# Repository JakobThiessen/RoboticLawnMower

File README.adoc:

= RoboticLawnMower
:TOC:

== Projektbeschreibung
Rasenmähroboter in Eigenbau

== Konzept

image::docs/Konzept_1.drawio.svg[static, 600]

== Projektübersicht

== Hardware
image::Hardware/KiCad/RoboticLawnMower/3D_TOP.png[static, 600]

image::Hardware/KiCad/RoboticLawnMower/3D_BOT.png[static, 600]

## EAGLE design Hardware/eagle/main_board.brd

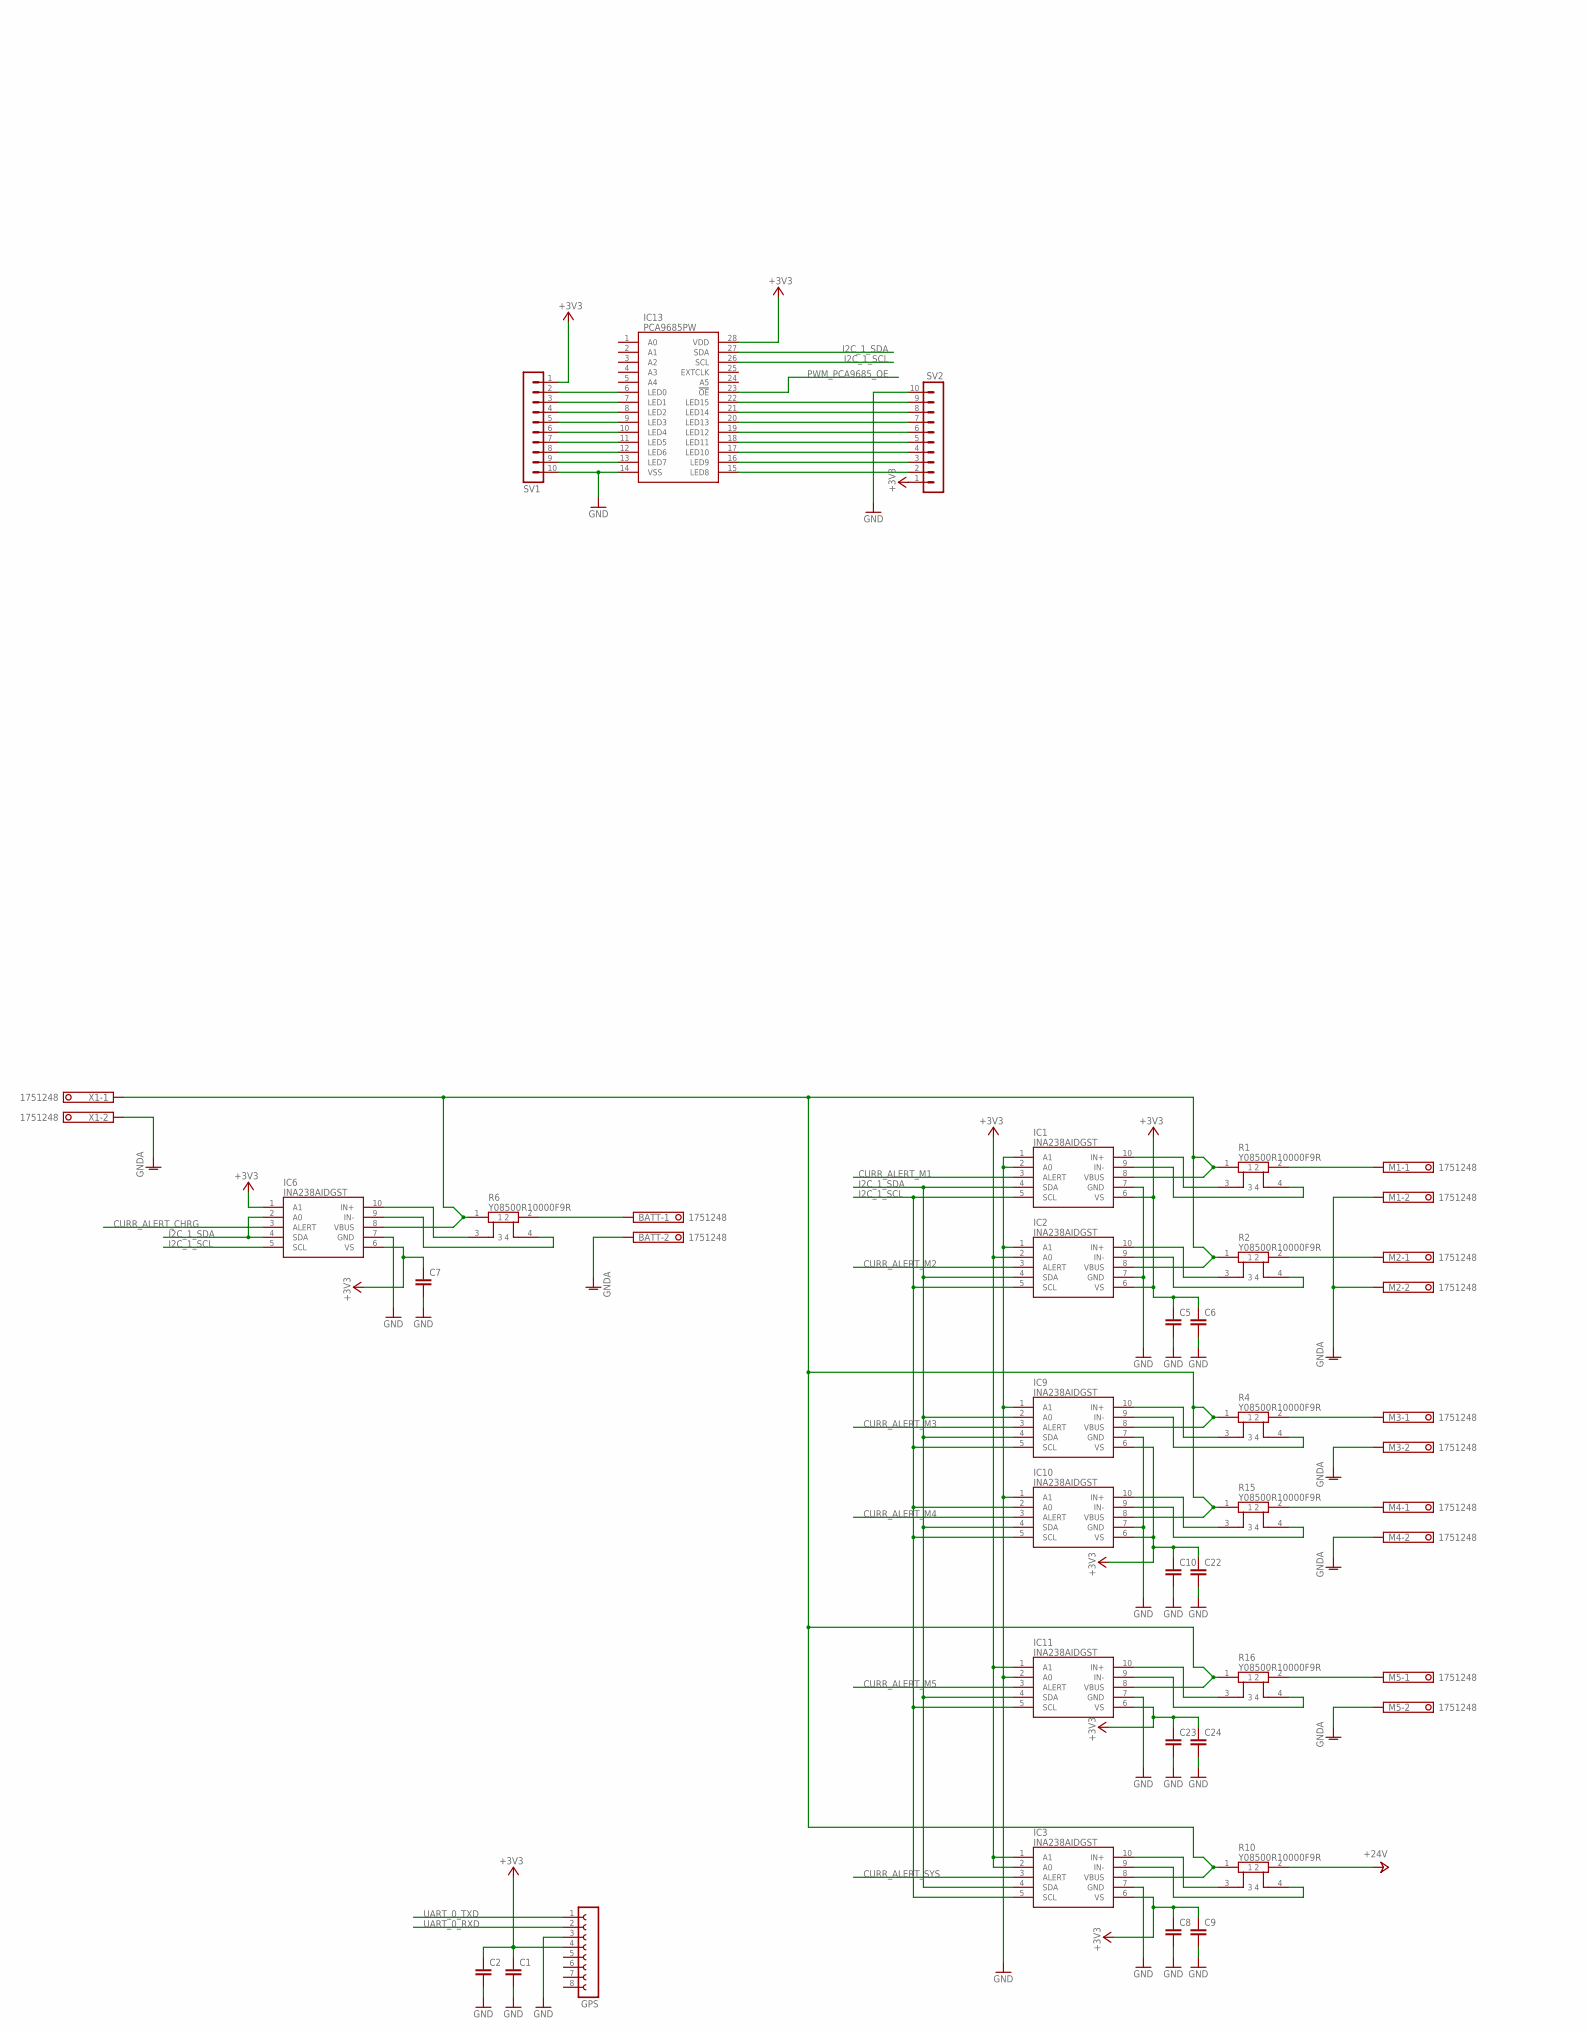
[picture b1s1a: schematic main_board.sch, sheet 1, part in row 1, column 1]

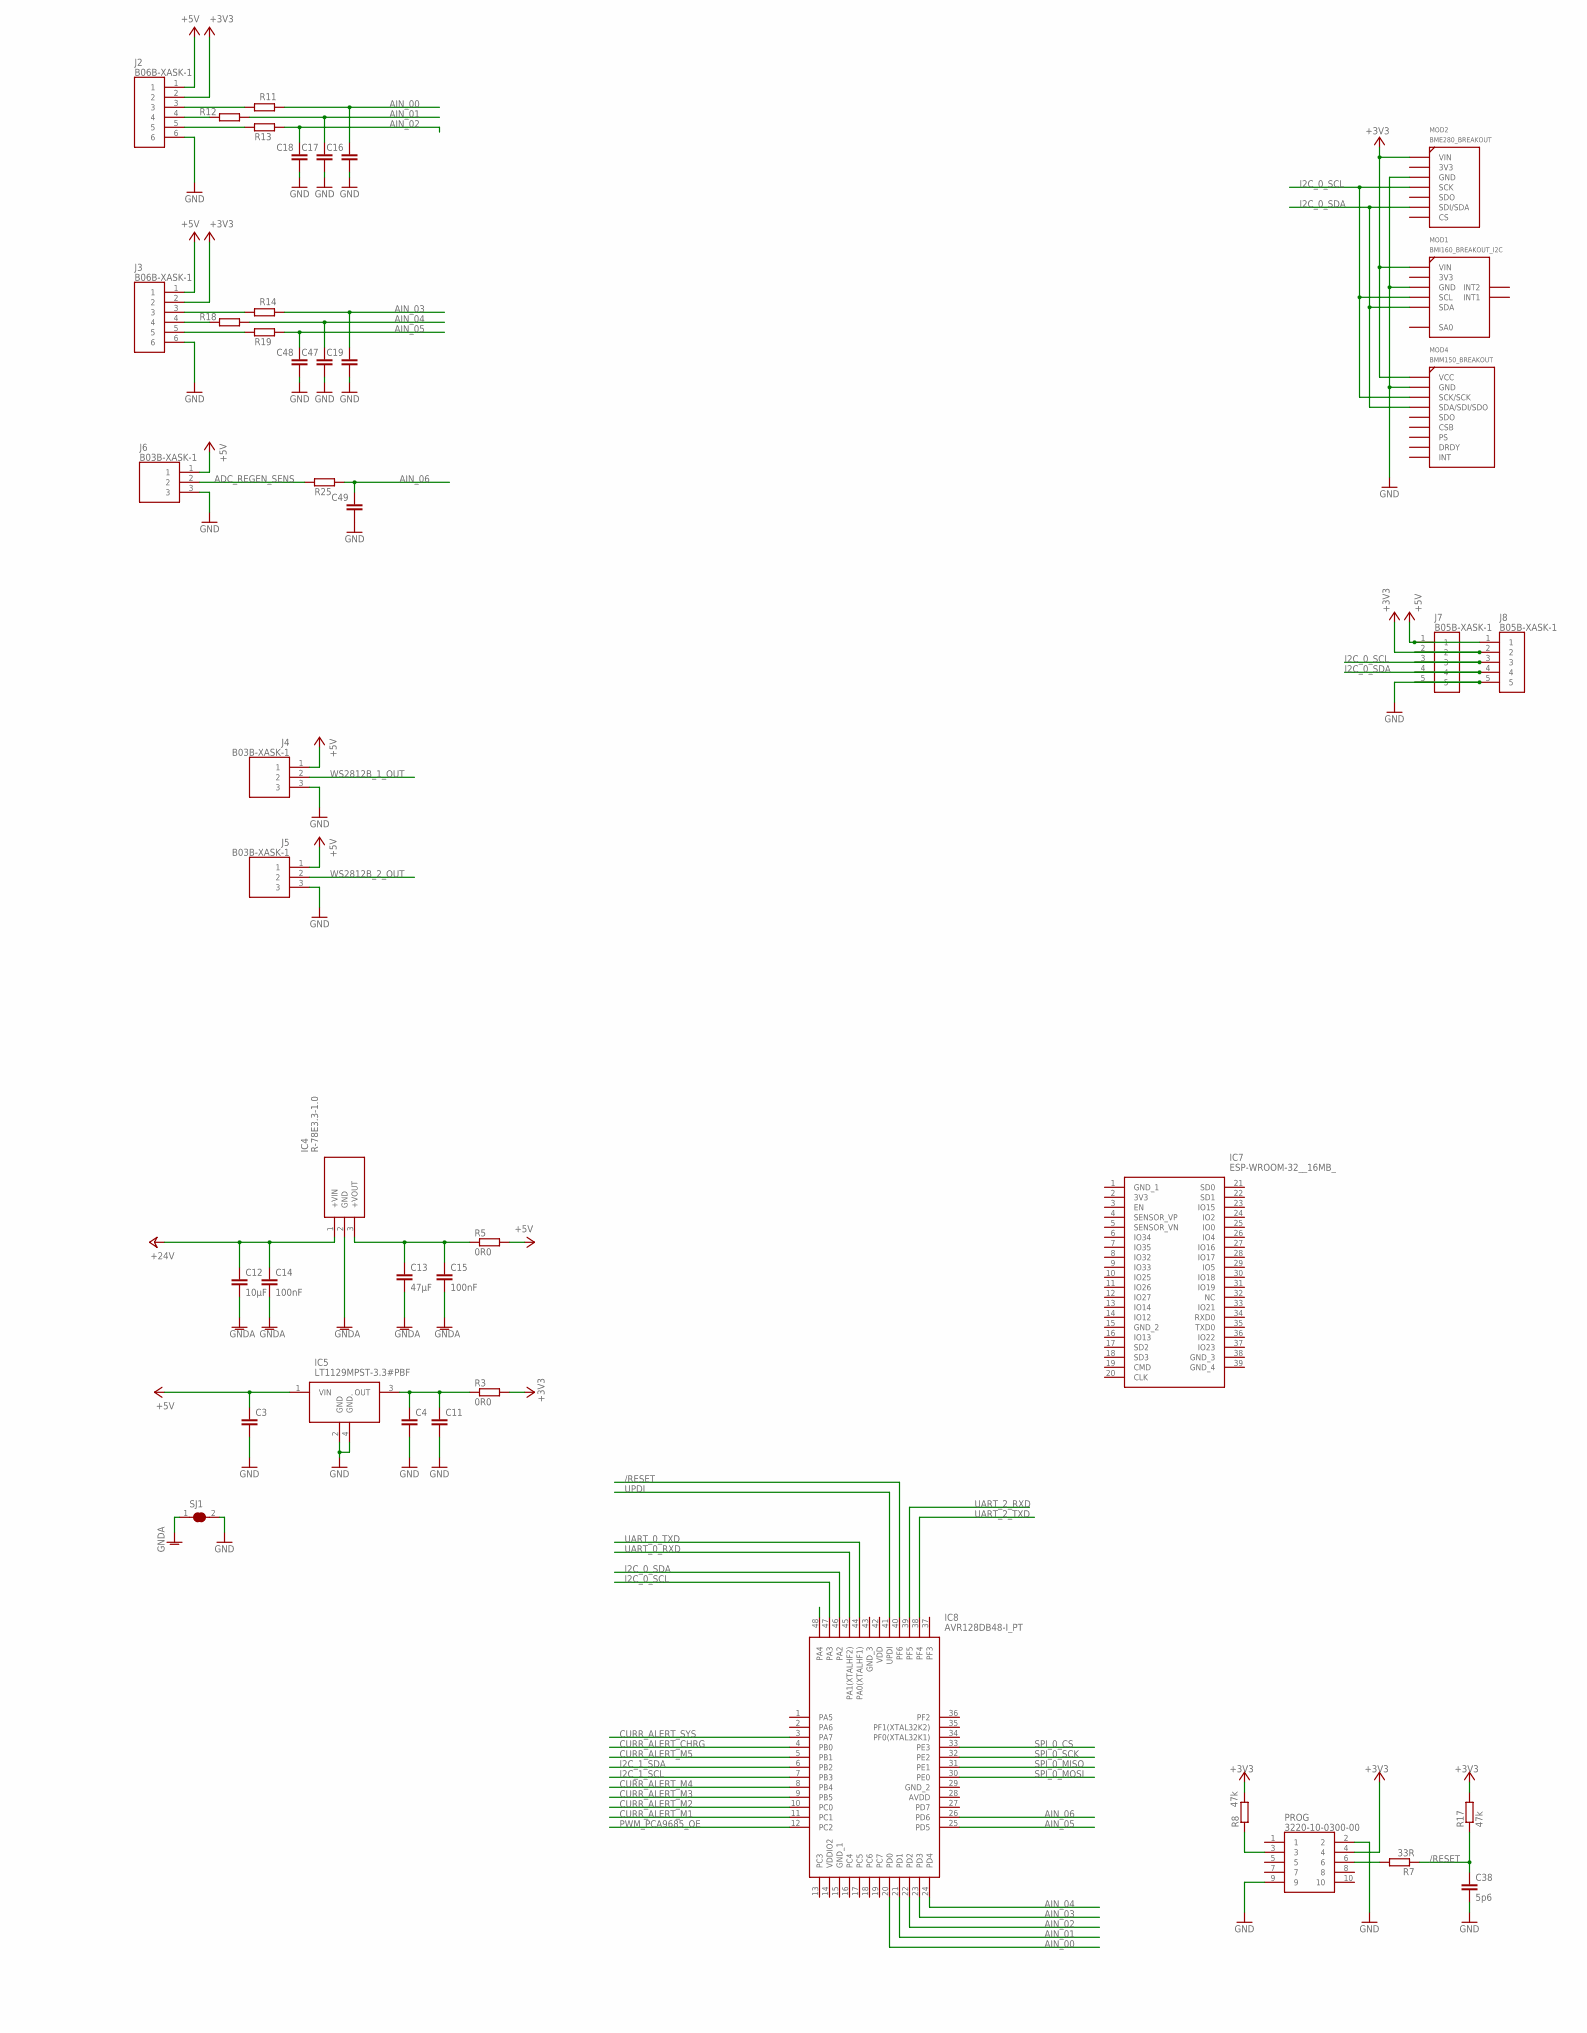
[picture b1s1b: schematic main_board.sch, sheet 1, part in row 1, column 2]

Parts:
BATT: 1751248
C1, C2, C3, C4, C5, C6, C7, C8, C9, C10, C11, C16, C17, C18, C19, C22, C23, C24, C47, C48, C49: C-EUC0603; C0603
C12: 10µF; C1210
C13: 47µF; C1210
C14, C15: 100nF; C0603
C38: 5p6; C0603
GPS: FE08-1; FE08
IC1, IC2, IC3, IC6, IC9, IC10, IC11: INA238AIDGST; SOP50P490X110-10N
IC4: R-78E3.3-1.0; R78E3310
IC5: LT1129MPST-3.3#PBF; SOT230P700X180-4N
IC7: ESP-WROOM-32__16MB_; ESP32WROOM32D
IC8: AVR128DB48-I_PT; QFP50P900X900X120-48N
IC13: PCA9685PW; SOP65P640X110-28N
J2, J3: B06B-XASK-1; SHDR6W60P0X250_1X6_1750X640X88
J4, J5, J6: B03B-XASK-1; SHDR3W60P0X250_1X3_1000X640X88
J7, J8: B05B-XASK-1; SHDR5W60P0X250_1X5_1500X640X88
M1, M2, M3, M4, M5: 1751248
MOD1: BMI160_BREAKOUT_I2C
MOD2: BME280_BREAKOUT
MOD4: BMM150_BREAKOUT
PROG: 3220-10-0300-00
R1, R2, R4, R6, R10, R15, R16: Y08500R10000F9R
R3, R5: 0R0; R0603
R7: 33R; R0603
R8, R17: 47k; R0603
R11, R12, R13, R14, R18, R19, R25: R-EU_R0603; R0603
SJ1: SOLDERJUMPER_CLOSEDPERM
SV1, SV2: MA10-1
X1: 1751248

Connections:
+3V3: C1.1, C2.1, C5.1, C6.1, C7.1, C8.1, C9.1, C10.1, C22.1, C23.1, C24.1, GPS.4, IC1.6 (VS), IC2.2 (A0), IC2.6 (VS), IC3.1 (A1), IC3.2 (A0), IC3.6 (VS), IC6.1 (A1), IC6.6 (VS), IC9.6 (VS), IC10.6 (VS), IC11.1 (A1), IC11.6 (VS), IC13.28 (VDD), J2.2, J3.2, J7.2, J8.2, MOD1.P$1 (VIN), MOD2.P$1 (VIN), MOD4.P$1 (VCC), PROG.4, R3.2, R8.2, R17.2, SV1.1, SV2.1
+5V: C3.1, IC5.1 (VIN), J2.1, J3.1, J4.1, J5.1, J6.1, J7.1, J8.1, R5.2
+24V: C12.1, C14.1, IC4.1 (+VIN), R10.2
+24V2: IC1.8 (VBUS), IC2.8 (VBUS), IC3.8 (VBUS), IC6.8 (VBUS), IC9.8 (VBUS), IC10.8 (VBUS), IC11.8 (VBUS), R1.1, R2.1, R4.1, R6.1, R10.1, R15.1, R16.1, X1.1
/RESET: C38.1, IC8.40 (PF6), R7.1, R17.1
ADC_REGEN_SENS: J6.2, R25.1
AIN_00: C16.1, IC8.20 (PD0), R11.2
AIN_01: C17.1, IC8.21 (PD1), R12.2
AIN_02: C18.1, IC8.22 (PD2), R13.2
AIN_03: C19.1, IC8.23 (PD3), R14.2
AIN_04: C47.1, IC8.24 (PD4), R18.2
AIN_05: C48.1, IC8.25 (PD5), R19.2
AIN_06: C49.1, IC8.26 (PD6), R25.2
CURR_ALERT_CHRG: IC6.3 (ALERT), IC8.4 (PB0)
CURR_ALERT_M1: IC1.3 (ALERT), IC8.11 (PC1)
CURR_ALERT_M2: IC2.3 (ALERT), IC8.10 (PC0)
CURR_ALERT_M3: IC8.9 (PB5), IC9.3 (ALERT)
CURR_ALERT_M4: IC8.8 (PB4), IC10.3 (ALERT)
CURR_ALERT_M5: IC8.5 (PB1), IC11.3 (ALERT)
CURR_ALERT_SYS: IC3.3 (ALERT), IC8.3 (PA7)
GND: C1.2, C2.2, C3.2, C4.2, C5.2, C6.2, C7.2, C8.2, C9.2, C10.2, C11.2, C16.2, C17.2, C18.2, C19.2, C22.2, C23.2, C24.2, C38.2, C47.2, C48.2, C49.2, GPS.3, IC1.1 (A1), IC1.2 (A0), IC1.7 (GND), IC2.1 (A1), IC2.7 (GND), IC3.7 (GND), IC5.2 (GND), IC5.4 (GND.), IC6.7 (GND), IC9.1 (A1), IC9.7 (GND), IC10.1 (A1), IC10.7 (GND), IC11.2 (A0), IC11.7 (GND), IC13.14 (VSS), J2.6, J3.6, J4.3, J5.3, J6.3, J7.5, J8.5, MOD1.P$3 (GND), MOD2.P$3 (GND), MOD4.P$2 (GND), PROG.2, PROG.9, SJ1.2, SV1.10, SV2.10
GNDA: BATT.2, C12.2, C13.2, C14.2, C15.2, IC4.2 (GND), M1.2, M2.2, M3.2, M4.2, M5.2, SJ1.1, X1.2
I2C_0_SCL: IC8.47 (PA3), J7.3, J8.3, MOD1.P$4 (SCL), MOD2.P$4 (SCK), MOD4.P$3 (SCK/SCK)
I2C_0_SDA: IC8.46 (PA2), J7.4, J8.4, MOD1.P$5 (SDA), MOD2.P$6 (SDI/SDA), MOD4.P$4 (SDA/SDI/SDO)
I2C_1_SCL: IC1.5 (SCL), IC2.5 (SCL), IC3.5 (SCL), IC6.5 (SCL), IC8.7 (PB3), IC9.5 (SCL), IC10.2 (A0), IC10.5 (SCL), IC11.5 (SCL), IC13.26 (SCL)
I2C_1_SDA: IC1.4 (SDA), IC2.4 (SDA), IC3.4 (SDA), IC6.2 (A0), IC6.4 (SDA), IC8.6 (PB2), IC9.2 (A0), IC9.4 (SDA), IC10.4 (SDA), IC11.4 (SDA), IC13.27 (SDA)
unnamed: M1.1, R1.2
unnamed: M2.1, R2.2
unnamed: M3.1, R4.2
unnamed: C4.1, C11.1, IC5.3 (OUT), R3.1
unnamed: C13.1, C15.1, IC4.3 (+VOUT), R5.1
unnamed: IC2.9 (IN-), R2.4
unnamed: IC1.9 (IN-), R1.4
unnamed: IC1.10 (IN+), R1.3
unnamed: IC6.9 (IN-), R6.4
unnamed: IC2.10 (IN+), R2.3
unnamed: IC6.10 (IN+), R6.3
unnamed: BATT.1, R6.2
unnamed: PROG.3, R8.1
unnamed: IC13.15 (LED8), SV2.2
unnamed: J2.4, R12.1
unnamed: PROG.6, R7.2
unnamed: J2.5, R13.1
unnamed: J2.3, R11.1
unnamed: IC13.6 (LED0), SV1.2
unnamed: IC3.9 (IN-), R10.4
unnamed: IC3.10 (IN+), R10.3
unnamed: M4.1, R15.2
unnamed: IC13.7 (LED1), SV1.3
unnamed: J3.4, R18.1
unnamed: IC10.9 (IN-), R15.4
unnamed: J3.5, R19.1
unnamed: IC9.9 (IN-), R4.4
unnamed: J3.3, R14.1
unnamed: IC9.10 (IN+), R4.3
unnamed: IC13.8 (LED2), SV1.4
unnamed: IC10.10 (IN+), R15.3
unnamed: M5.1, R16.2
unnamed: IC11.9 (IN-), R16.4
unnamed: IC11.10 (IN+), R16.3
unnamed: IC13.9 (LED3), SV1.5
unnamed: IC13.10 (LED4), SV1.6
unnamed: IC13.11 (LED5), SV1.7
unnamed: IC13.12 (LED6), SV1.8
unnamed: IC13.13 (LED7), SV1.9
unnamed: IC13.16 (LED9), SV2.3
unnamed: IC13.17 (LED10), SV2.4
unnamed: IC13.18 (LED11), SV2.5
unnamed: IC13.19 (LED12), SV2.6
unnamed: IC13.20 (LED13), SV2.7
unnamed: IC13.21 (LED14), SV2.8
unnamed: IC13.22 (LED15), SV2.9
PWM_PCA9685_OE: IC8.12 (PC2), IC13.23 (!OE)
SPI_0_CS: IC8.33 (PE3)
SPI_0_MISO: IC8.31 (PE1)
SPI_0_MOSI: IC8.30 (PE0)
SPI_0_SCK: IC8.32 (PE2)
UART_0_RXD: GPS.2, IC8.45 (PA1(XTALHF2))
UART_0_TXD: GPS.1, IC8.44 (PA0(XTALHF1))
UART_2_RXD: IC8.39 (PF5)
UART_2_TXD: IC8.38 (PF4)
UPDI: IC8.41 (UPDI)
WS2812B_1_OUT: J4.2
WS2812B_2_OUT: J5.2

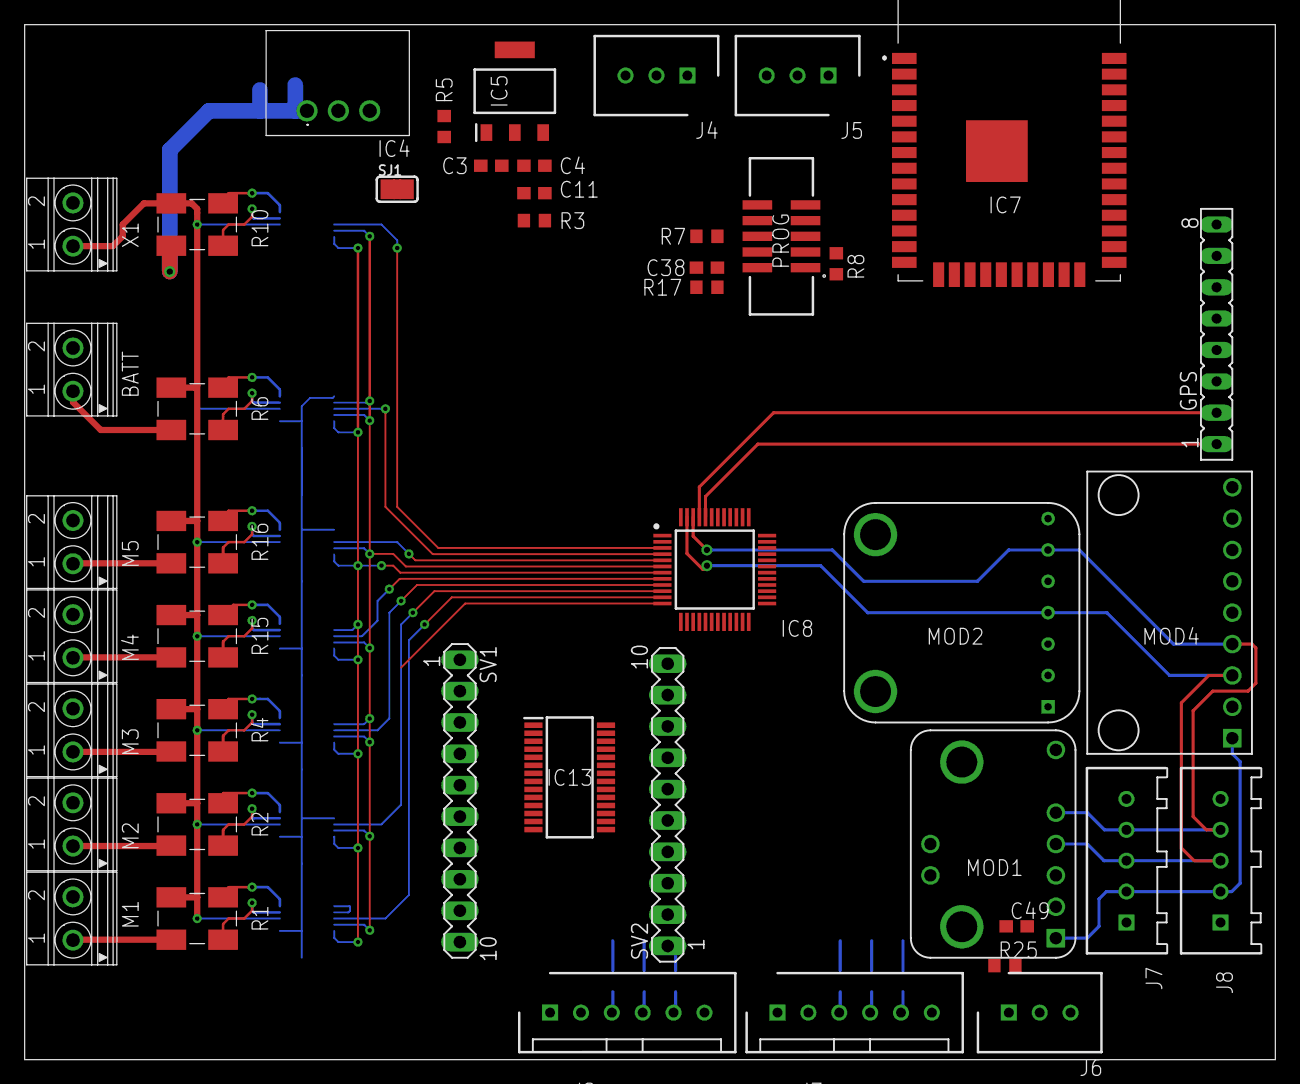
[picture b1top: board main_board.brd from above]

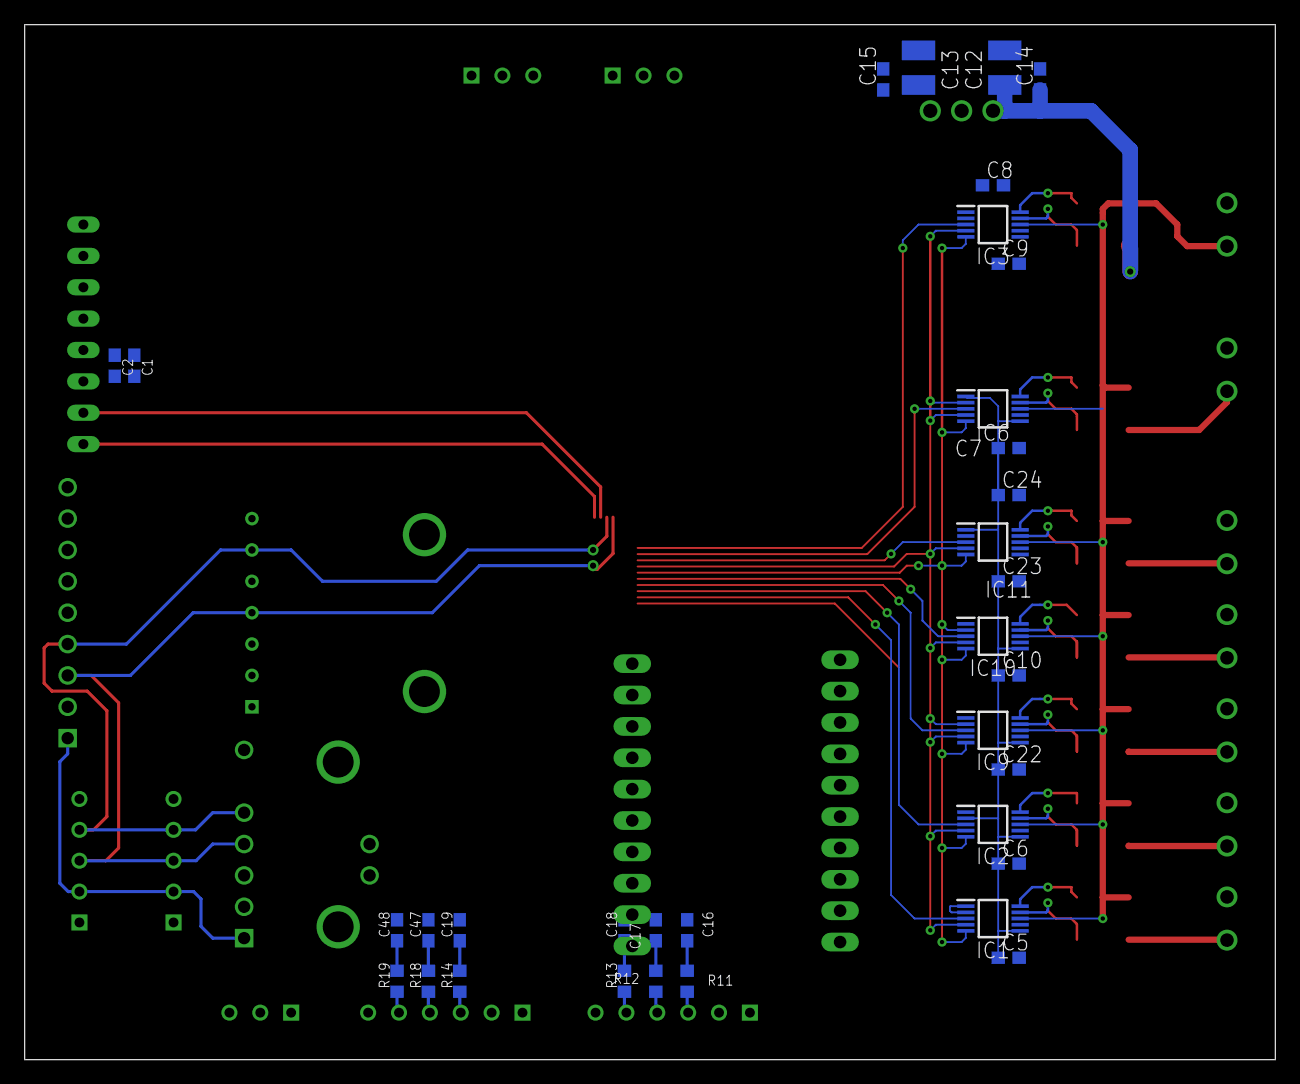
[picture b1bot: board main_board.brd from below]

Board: 2 copper layers, 101.3 x 83.8 mm, 79 parts (34 on the bottom side), 75 nets.

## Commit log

2022-10-18 Schaltplan hinzugefügt. Erster entwurf
2022-10-21 main_board.brd - Layout
2022-10-22 Layout
2022-10-31 layout update
2022-11-01 schaltplan und layout
2023-01-21 bild hinzugefügt.
2023-01-23 Konzept bild angepasst
2023-01-24 Systemkonzept angepasst
2023-01-25 konzept
2023-02-04 Schaltplan und Layout änderung
2023-02-06 readme angepasst
2023-02-07 readme
2023-02-08 Schaltplan & Layout Änderung
2023-02-08 readme Änderung
2023-02-11 Layout ready add gerber file
2023-02-28 kleine Änderung
2023-02-28 projekt aufgeräumt
2023-02-28 add embedded project
2023-03-01 add driver - BMM150 - INA228
2023-03-04 driver
2023-03-07 bugFix driver BMI160 BMM150
2023-03-07 bug fix bmm150 bmi160
2023-03-11 add pca9685 driver
2023-03-12 add gps/nmea driver
2023-03-19 add TMAG5273 driver add lwgps driver
2023-03-27 FreeRTOS
2023-07-30 add gps communcation on usart3
2023-07-30 save files with KiCad 7.0
2023-08-03 firmware angepassst LabVIew Projekt erstellt
2023-08-17 LAbView Projekt angepasst
2023-09-11 LabView projekt angepasst Embedded: - Treiber für VL53L1X hinzugefügt (Nicht ganz fertig)
2023-09-11 implement driver: - VL53L1X
2023-09-12 Motor L und R läuft Abstandsensor läuft Kollision läuft
2023-09-17 State Machine für den Ablauf.
2023-10-08 add perimeter sender
2024-06-02 Redesign: - Controller - I2C pinning geändert - uvm
2024-06-02 Schaltplan hinzugefügt RS485 Lib hinzugefügt
2024-06-02 hinterrad 3d model
2024-06-03 änderung
2025-04-07 change µC to STM32H573
2025-04-11 Layout fertig, Gerber-Datei muss noch erzeugt werden.
2025-04-11 Dokumentation
2025-04-14 Levelshift für MotorSignal zum µC
2025-04-14 gerberdaten erzeugt

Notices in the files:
parts and their libraries:
microbuilder: This work is placed in the public domain, and may be freely used for commercial and non-commercial work with the following conditions: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
